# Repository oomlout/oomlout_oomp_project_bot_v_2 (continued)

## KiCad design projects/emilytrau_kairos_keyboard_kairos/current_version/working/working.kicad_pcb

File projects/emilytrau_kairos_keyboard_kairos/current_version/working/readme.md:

# kairos_keyboard
 
## summary 
* id: emilytrau_kairos_keyboard_kairos
* user: emilytrau
* name: kairos_keyboard
* board: kairos
* repo: https://github.com/emilytrau/Kairos_Keyboard
* src_file_repo_kicad_pcb: Kairos.kicad_pcb
* src_file_repo_kicad_pcb_link: https://github.com/emilytrau/Kairos_Keyboard/tree/master/Kairos.kicad_pcb

* src_file_repo_sch: Kairos.sch
* src_file_repo_sch_link: https://github.com/emilytrau/Kairos_Keyboard/tree/master/Kairos.sch
* full details link: https://github.com/oomlout/oomlout_oomp_project_bot_v_2/tree/main/projects/emilytrau_kairos_keyboard_kairos/current_version/working

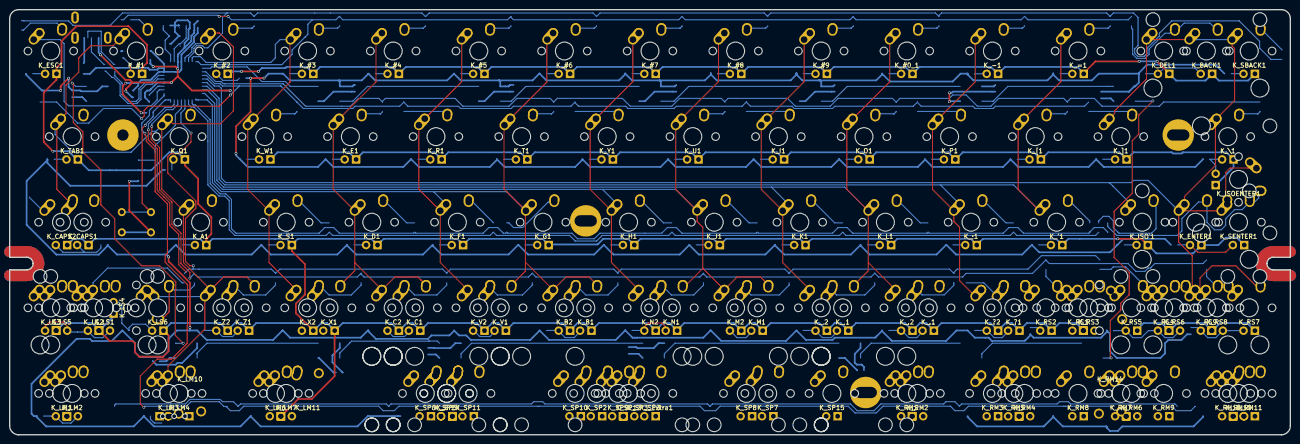
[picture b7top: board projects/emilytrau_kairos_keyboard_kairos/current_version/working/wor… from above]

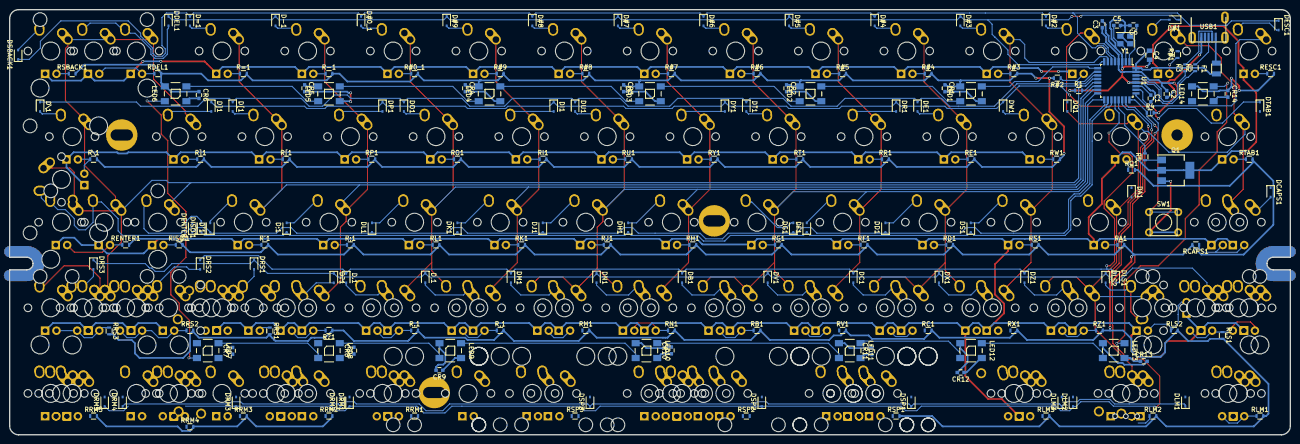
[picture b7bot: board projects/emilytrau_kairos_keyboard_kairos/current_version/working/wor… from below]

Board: 2 copper layers, 285.0 x 94.6 mm, 300 parts (183 on the bottom side), 185 nets.

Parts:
C1: 1uF; C_0603
C2, C3: 100nF; C_0603
C4: 4.7uF; C_0805
C5, C6: 22pF; C_0603
CR1, CR2, CR3, CR4, CR5, CR6, CR7, CR8, CR9, CR10, CR11, CR12, CR13, CR14: 100nF; C_0603
D#0_1, D#1, D#2, D#3, D#4, D#5, D#6, D#7, D#8, D#9: 1N4148WS; D_SOD-323
D'1: 1N4148WS; D_SOD-323
D,1: 1N4148WS; D_SOD-323
D-1: 1N4148WS; D_SOD-323
D.1: 1N4148WS; D_SOD-323
D;1: 1N4148WS; D_SOD-323
D=1: 1N4148WS; D_SOD-323
D?1: 1N4148WS; D_SOD-323
DA1: 1N4148WS; D_SOD-323
DB1: 1N4148WS; D_SOD-323
DC1: 1N4148WS; D_SOD-323
DCAPS1: 1N4148WS; D_SOD-323
DD1: 1N4148WS; D_SOD-323
DDEL1: 1N4148WS; D_SOD-323
DE1: 1N4148WS; D_SOD-323
DENTER1: 1N4148WS; D_SOD-323
DESC1: 1N4148WS; D_SOD-323
DF1: 1N4148WS; D_SOD-323
DG1: 1N4148WS; D_SOD-323
DH1: 1N4148WS; D_SOD-323
DI1: 1N4148WS; D_SOD-323
DISO`1: 1N4148WS; D_SOD-323
DJ1: 1N4148WS; D_SOD-323
DK1: 1N4148WS; D_SOD-323
DL1: 1N4148WS; D_SOD-323
DLM1, DLM2, DLM3: 1N4148WS; D_SOD-323
DLS1, DLS2: 1N4148WS; D_SOD-323
DM1: 1N4148WS; D_SOD-323
DN1: 1N4148WS; D_SOD-323
DO1: 1N4148WS; D_SOD-323
DP1: 1N4148WS; D_SOD-323
DQ1: 1N4148WS; D_SOD-323
DR1: 1N4148WS; D_SOD-323
DRM1, DRM2, DRM3, DRM4, DRM5: 1N4148WS; D_SOD-323
DRS1, DRS2, DRS3: 1N4148WS; D_SOD-323
DS1: 1N4148WS; D_SOD-323
DSBACK1: 1N4148WS; D_SOD-323
DSP1, DSP2, DSP3: 1N4148WS; D_SOD-323
DT1: 1N4148WS; D_SOD-323
DTAB1: 1N4148WS; D_SOD-323
DU1: 1N4148WS; D_SOD-323
DV1: 1N4148WS; D_SOD-323
DW1: 1N4148WS; D_SOD-323
DX1: 1N4148WS; D_SOD-323
DY1: 1N4148WS; D_SOD-323
DZ1: 1N4148WS; D_SOD-323
D[1: 1N4148WS; D_SOD-323
D\1: 1N4148WS; D_SOD-323
D]1: 1N4148WS; D_SOD-323
F1: Polyfuse; Fuse_SMD1206_Reflow
K_#0_1, K_#1, K_#2, K_#3, K_#4, K_#5, K_#6, K_#7, K_#8, K_#9: MX-1U
K_'1: MX-1U
K_,1: MX-1U-FLIPPED; MX-1U
K_,2: MX-1U
K_-1: MX-1U
K_.1: MX-1U-FLIPPED; MX-1U
K_.2: MX-1U
K_;1: MX-1U
K_=1: MX-1U
K_?1: MX-1U-FLIPPED; MX-1U
K_?2: MX-1U
K_A1: MX-1U
K_B1: MX-1U-FLIPPED; MX-1U
K_B2: MX-1U
K_BACK1: MX-2U
K_C1: MX-1U-FLIPPED; MX-1U
K_C2: MX-1U
K_CAPS1: MX-1.75U
K_CAPS2: MX-1.25U
K_D1: MX-1U
K_DEL1: MX-1U
K_E1: MX-1U
K_ENTER1: MX-2.25U
K_ESC1: MX-1U
K_F1: MX-1U
K_G1: MX-1U
K_H1: MX-1U
K_I1: MX-1U
K_ISOENTER1: MX-ISO-FLIPPED; MX-ISO-Combined
K_ISO`1: MX-1U
K_J1: MX-1U
K_K1: MX-1U
K_L1: MX-1U
K_LM1, K_LM6: MX-1.25U
K_LM2, K_LM7: MX-1.5U; MX-1.5U-FLIPPED
K_LM3: MX-1.25U; MX-1.25U-FLIPPED
K_LM4: MX-1U
K_LM10: MX-1.25U; ALPS-1.25U
K_LM11: MX-1.5U-FLIPPED; ALPS-1.5U
K_LS1: MX-2.25U-FLIPPED
K_LS2: MX-2U-FLIPPED; MX-2U
K_LS3, K_LS4, K_LS6: MX-1U
K_LS5: MX-1.25U; MX-1.25U-FLIPPED
K_M1: MX-1U-FLIPPED; MX-1U
K_M2: MX-1U
K_N1: MX-1U-FLIPPED; MX-1U
K_N2: MX-1U
K_O1: MX-1U
K_P1: MX-1U
K_Q1: MX-1U
K_R1: MX-1U
K_RM1, K_RM7, K_RM11: MX-1U
K_RM2, K_RM4, K_RM6, K_RM10: MX-1.25U; MX-1.25U-FLIPPED
K_RM3, K_RM8, K_RM9: MX-1U-FLIPPED; MX-1U
K_RM5, K_RM12: MX-1.5U
K_RM14: MX-1.25U; ALPS-1.25U
K_RS1, K_RS4, K_RS7: MX-1U-FLIPPED; MX-1U
K_RS2, K_RS5: MX-1.75U
K_RS3: MX-1.25U-FLIPPED
K_RS6: MX-2.75U-FLIPPED
K_RS8: MX-1.75U; MX-1.75U-FLIPPED
K_RS9: MX-2U
K_RS10: KEYSW; MX_100
K_S1: MX-1U
K_SBACK1: MX-1U
K_SENTER1: MX-1.25U; MX-1U
K_SP2: MX-6.25U; MX-6.25U-ReversedStabilizers
K_SP3: MX-7U; MX-7U-ReversedStabilizers
K_SP3_Extra1: MX-6U; MX-6U-7UOverlay
K_SP5: MX-2.75U; MX-2.75U-ReversedStabilizer
K_SP6: MX-2.25U-FLIPPED; MX-2.25U-ReversedStabilizer
K_SP7, K_SP14: MX-2.25U; MX-2.25U-ReversedStabilizer
K_SP8, K_SP11, K_SP15: MX-2.75U-FLIPPED; MX-2.75U-ReversedStabilizer
K_SP9, K_SP10: MX-1.25U-FLIPPED; MX-1.25U
K_SP13: MX-2U-FLIPPED; MX-2U-ReversedStabilizers-FLIPPED
K_T1: MX-1U
K_TAB1: MX-1.5U
K_U1: MX-1U
K_V1: MX-1U-FLIPPED; MX-1U
K_V2: MX-1U
K_W1: MX-1U
K_X1: MX-1U-FLIPPED; MX-1U
K_X2: MX-1U
K_Y1: MX-1U
K_Z1: MX-1U-FLIPPED; MX-1U
K_Z2: MX-1U
K_[1: MX-1U
K_\1: MX-1.5U
K_]1: MX-1U
LED1, LED2, LED3, LED4, LED5, LED6, LED7, LED8, LED9, LED10, LED11, LED12, LED13, LED14: WS2812B
Q1: NSS40301MZ4T1G; SOT-223-3Lead_TabPin2
R1, R4: 10k; R_0603
R2, R3: 22; R_0603
R5: 1.5k; R_0603
R#0_1, R#1, R#2, R#3, R#4, R#5, R#6, R#7, R#8, R#9: 2.2k; R_0603
R'1: 2.2k; R_0603
R,1: 2.2k; R_0603
R-1: 2.2k; R_0603
R.1: 2.2k; R_0603
R;1: 2.2k; R_0603
R=1: 2.2k; R_0603
R?1: 2.2k; R_0603
RA1: 2.2k; R_0603
RB1: 2.2k; R_0603
RC1: 2.2k; R_0603
RCAPS1: 2.2k; R_0603
RD1: 2.2k; R_0603
RDEL1: 2.2k; R_0603
RE1: 2.2k; R_0603
RENTER1: 2.2k; R_0603
RESC1: 2.2k; R_0603
RF1: 2.2k; R_0603
RG1: 2.2k; R_0603
RH1: 2.2k; R_0603
RI1: 2.2k; R_0603
RISO`1: 2.2k; R_0603
RJ1: 2.2k; R_0603
RK1: 2.2k; R_0603
RL1: 2.2k; R_0603
RLM1, RLM2, RLM3: 2.2k; R_0603
RLS1, RLS2: 2.2k; R_0603
RM1: 2.2k; R_0603
RN1: 2.2k; R_0603
RO1: 2.2k; R_0603
RP1: 2.2k; R_0603
RQ1: 2.2k; R_0603
RR1: 2.2k; R_0603
RRM1, RRM2, RRM3, RRM4, RRM5: 2.2k; R_0603
RRS1, RRS2, RRS3: 2.2k; R_0603
RS1: 2.2k; R_0603
RSBACK1: 2.2k; R_0603
RSP1, RSP2, RSP3: 2.2k; R_0603
RT1: 2.2k; R_0603
RTAB1: 2.2k; R_0603
RU1: 2.2k; R_0603
RV1: 2.2k; R_0603
RW1: 2.2k; R_0603
RX1: 2.2k; R_0603
RY1: 2.2k; R_0603
RZ1: 2.2k; R_0603
R[1: 2.2k; R_0603
R\1: 2.2k; R_0603
R]1: 2.2k; R_0603
SW1: SW_RST1; PushButton_6x6mm_TH
U1: ATMEGA32U2-AU; TQFP-32_7x7mm_Pitch0.8mm
USB1: Molex-0548190589
Y1: Crystal_GND24; Crystal_SMD_3225-4pin_3.2x2.5mm

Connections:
+5V: C2.1, C3.1, C4.1, CR1.1, CR2.1, CR3.1, CR4.1, CR5.1, CR6.1, CR7.1, CR8.1, CR9.1, CR10.1, CR11.1, CR12.1, CR13.1, CR14.1, F1.1, LED1.1, LED2.1, LED3.1, LED4.1, LED5.1, LED6.1, LED7.1, LED8.1, LED9.1, LED10.1, LED11.1, LED12.1, LED13.1, LED14.1, R4.2, R#0_1.2, R#1.2, R#2.2, R#3.2, R#4.2, R#5.2, R#6.2, R#7.2, R#8.2, R#9.2, R'1.2, R,1.2, R-1.2, R.1.2, R;1.2, R=1.2, R?1.1, RA1.2, RB1.2, RC1.2, RCAPS1.2, RD1.2, RDEL1.2, RE1.2, RENTER1.2, RESC1.2, RF1.2, RG1.2, RH1.2, RI1.2, RISO`1.2, RJ1.2, RK1.2, RL1.2, RLM1.2, RLM2.2, RLM3.2, RLS1.2, RLS2.2, RM1.2, RN1.2, RO1.2, RP1.2, RQ1.2, RR1.2, RRM1.2, RRM2.2, RRM3.2, RRM4.2, RRM5.2, RRS1.2, RRS2.2, RRS3.2, RS1.2, RSBACK1.2, RSP1.2, RSP2.2, RSP3.2, RT1.2, RTAB1.2, RU1.2, RV1.2, RW1.2, RX1.2, RY1.2, RZ1.2, R[1.2, R\1.2, R]1.2, U1.4, U1.31, U1.32
COL0: K_ESC1.1, K_LM1.1, K_LM2.1, K_LS1.2, K_LS2.2, K_LS3.1, K_LS5.1, U1.26
COL1: K_#1.1, K_#2.1, K_A1.1, K_CAPS1.1, K_CAPS2.2, K_LM3.1, K_LM4.1, K_LM6.1, K_LM7.1, K_LM10.1, K_LM11.2, K_LS4.1, K_LS6.1, K_Q1.1, K_TAB1.1, K_Z1.2, K_Z2.1, U1.5
COL2: K_#3.1, K_#4.1, K_C1.2, K_C2.1, K_D1.1, K_E1.1, K_S1.1, K_W1.1, K_X1.2, K_X2.1, U1.7
COL3: K_#5.1, K_#6.1, K_B1.2, K_B2.1, K_F1.1, K_G1.1, K_R1.1, K_SP2.1, K_SP3.1, K_SP5.1, K_SP6.2, K_SP9.2, K_SP10.2, K_SP11.2, K_SP13.2, K_SP14.1, K_T1.1, K_V1.2, K_V2.1, U1.17
COL4: K_#7.1, K_#8.1, K_H1.1, K_J1.1, K_M1.2, K_M2.1, K_N1.2, K_N2.1, K_SP7.1, K_SP8.2, K_SP15.2, K_U1.1, K_Y1.1, U1.16
COL5: K_#0_1.1, K_#9.1, K_,1.2, K_,2.1, K_.1.2, K_.2.1, K_I1.1, K_K1.1, K_L1.1, K_O1.1, K_RM1.1, K_RM2.1, U1.15
COL6: K_'1.1, K_-1.1, K_;1.1, K_=1.1, K_?1.2, K_?2.1, K_P1.1, K_RM3.2, K_RM4.1, K_RM5.1, K_RM8.2, K_RS1.2, K_RS2.1, K_RS3.2, K_[1.1, U1.14
COL7: K_BACK1.1, K_DEL1.1, K_ENTER1.1, K_ISOENTER1.2, K_ISO`1.1, K_RM6.1, K_RM7.1, K_RM9.2, K_RM10.1, K_RM11.1, K_RM12.1, K_RM14.1, K_RS4.2, K_RS5.1, K_RS6.2, K_RS7.2, K_RS8.1, K_RS9.1, K_RS10.2, K_SBACK1.1, K_SENTER1.1, K_\1.1, K_]1.1, U1.12
DM: R3.2, USB1.4
DP: R2.2, USB1.3
GND: C1.2, C2.2, C3.2, C4.2, C5.2, C6.2, CR1.2, CR2.2, CR3.2, CR4.2, CR5.2, CR6.2, CR7.2, CR8.2, CR9.2, CR10.2, CR11.2, CR12.2, CR13.2, CR14.2, LED1.3, LED2.3, LED3.3, LED4.3, LED5.3, LED6.3, LED7.3, LED8.3, LED9.3, LED10.3, LED11.3, LED12.3, LED13.3, LED14.3, Q1.3, R1.1, SW1.1, U1.3, U1.28, USB1.1, Y1.2, Y1.4
LEDGND: K_#0_1.4, K_#1.4, K_#2.4, K_#3.4, K_#4.4, K_#5.4, K_#6.4, K_#7.4, K_#8.4, K_#9.4, K_'1.4, K_,1.4, K_,2.4, K_-1.4, K_.1.4, K_.2.4, K_;1.4, K_=1.4, K_?1.4, K_?2.4, K_A1.4, K_B1.4, K_B2.4, K_BACK1.4, K_C1.4, K_C2.4, K_CAPS1.4, K_CAPS2.4, K_D1.4, K_DEL1.4, K_E1.4, K_ENTER1.4, K_ESC1.4, K_F1.4, K_G1.4, K_H1.4, K_I1.4, K_ISOENTER1.4, K_ISO`1.4, K_J1.4, K_K1.4, K_L1.4, K_LM1.4, K_LM2.4, K_LM3.4, K_LM6.4, K_LM7.4, K_LS1.4, K_LS2.4, K_LS3.4, K_LS4.4, K_LS5.4, K_LS6.4, K_M1.4, K_M2.4, K_N1.4, K_N2.4, K_O1.4, K_P1.4, K_Q1.4, K_R1.4, K_RM1.4, K_RM2.4, K_RM3.4, K_RM4.4, K_RM5.4, K_RM6.4, K_RM7.4, K_RM8.4, K_RM9.4, K_RM10.4, K_RM11.4, K_RM12.4, K_RS1.4, K_RS2.4, K_RS3.4, K_RS4.4, K_RS5.4, K_RS6.4, K_RS7.4, K_RS8.4, K_RS9.4, K_S1.4, K_SBACK1.4, K_SENTER1.4, K_SP2.4, K_SP3.4, K_SP5.4, K_SP6.4, K_SP7.4, K_SP8.4, K_SP9.4, K_SP10.4, K_SP11.4, K_SP13.4, K_SP14.4, K_SP15.4, K_T1.4, K_TAB1.4, K_U1.4, K_V1.4, K_V2.4, K_W1.4, K_X1.4, K_X2.4, K_Y1.4, K_Z1.4, K_Z2.4, K_[1.4, K_\1.4, K_]1.4, Q1.2
unnamed: C1.1, U1.27
unnamed: C5.1, U1.2, Y1.3
unnamed: C6.1, U1.1, Y1.1
unnamed: D#0_1.2, K_#0_1.2
unnamed: D#1.2, K_#1.2
unnamed: D#2.2, K_#2.2
unnamed: D#3.2, K_#3.2
unnamed: D#4.2, K_#4.2
unnamed: D#5.2, K_#5.2
unnamed: D#6.2, K_#6.2
unnamed: D#7.2, K_#7.2
unnamed: D#8.2, K_#8.2
unnamed: D#9.2, K_#9.2
unnamed: D'1.2, K_'1.2
unnamed: D,1.2, K_,1.1, K_,2.2
unnamed: D-1.2, K_-1.2
unnamed: D.1.2, K_.1.1, K_.2.2
unnamed: D;1.2, K_;1.2
unnamed: D=1.2, K_=1.2
unnamed: D?1.2, K_?1.1, K_?2.2
unnamed: DA1.2, K_A1.2
unnamed: DB1.2, K_B1.1, K_B2.2
unnamed: DC1.2, K_C1.1, K_C2.2
unnamed: DCAPS1.2, K_CAPS1.2, K_CAPS2.1
unnamed: DD1.2, K_D1.2
unnamed: DDEL1.2, K_BACK1.2, K_DEL1.2
unnamed: DE1.2, K_E1.2
unnamed: DENTER1.2, K_ENTER1.2, K_ISOENTER1.1, K_SENTER1.2
unnamed: DESC1.2, K_ESC1.2
unnamed: DF1.2, K_F1.2
unnamed: DG1.2, K_G1.2
unnamed: DH1.2, K_H1.2
unnamed: DI1.2, K_I1.2
unnamed: DISO`1.2, K_ISO`1.2
unnamed: DJ1.2, K_J1.2
unnamed: DK1.2, K_K1.2
unnamed: DL1.2, K_L1.2
unnamed: DLM1.2, K_LM1.2, K_LM2.2
unnamed: DLM2.2, K_LM3.2, K_LM4.2, K_LM10.2
unnamed: DLM3.2, K_LM6.2, K_LM7.2, K_LM11.1
unnamed: DLS1.2, K_LS1.1, K_LS2.1, K_LS3.2, K_LS5.2
unnamed: DLS2.2, K_LS4.2, K_LS6.2
unnamed: DM1.2, K_M1.1, K_M2.2
unnamed: DN1.2, K_N1.1, K_N2.2
unnamed: DO1.2, K_O1.2
unnamed: DP1.2, K_P1.2
unnamed: DQ1.2, K_Q1.2
unnamed: DR1.2, K_R1.2
unnamed: DRM1.2, K_RM1.2, K_RM2.2
unnamed: DRM2.2, K_RM3.1, K_RM4.2, K_RM5.2
unnamed: DRM3.2, K_RM8.1
unnamed: DRM4.2, K_RM6.2, K_RM7.2, K_RM9.1, K_RM14.2
unnamed: DRM5.2, K_RM10.2, K_RM11.2, K_RM12.2
unnamed: DRS1.2, K_RS1.1, K_RS2.2, K_RS3.1
unnamed: DRS2.2, K_RS4.1, K_RS5.2, K_RS6.1, K_RS10.1
unnamed: DRS3.2, K_RS7.1, K_RS8.2, K_RS9.2
unnamed: DS1.2, K_S1.2
unnamed: DSBACK1.2, K_SBACK1.2
unnamed: DSP1.2, K_SP5.2, K_SP6.1, K_SP11.1, K_SP14.2
unnamed: DSP2.2, K_SP2.2, K_SP3.2, K_SP9.1, K_SP10.1, K_SP13.1
unnamed: DSP3.2, K_SP7.2, K_SP8.1, K_SP15.1
unnamed: DT1.2, K_T1.2
unnamed: DTAB1.2, K_TAB1.2
unnamed: DU1.2, K_U1.2
unnamed: DV1.2, K_V1.1, K_V2.2
unnamed: DW1.2, K_W1.2
unnamed: DX1.2, K_X1.1, K_X2.2
unnamed: DY1.2, K_Y1.2
unnamed: DZ1.2, K_Z1.1, K_Z2.2
unnamed: D[1.2, K_[1.2
unnamed: D\1.2, K_\1.2
unnamed: D]1.2, K_]1.2
unnamed: K_#0_1.3, R#0_1.1
unnamed: K_#1.3, R#1.1
unnamed: K_#2.3, R#2.1
unnamed: K_#3.3, R#3.1
unnamed: K_#4.3, R#4.1
unnamed: K_#5.3, R#5.1
unnamed: K_#6.3, R#6.1
unnamed: K_#7.3, R#7.1
unnamed: K_#8.3, R#8.1
unnamed: K_#9.3, R#9.1
unnamed: K_'1.3, R'1.1
unnamed: K_,1.3, K_,2.3, R,1.1
unnamed: K_-1.3, R-1.1
unnamed: K_.1.3, K_.2.3, R.1.1
unnamed: K_;1.3, R;1.1
unnamed: K_=1.3, R=1.1
unnamed: K_?1.3, K_?2.3, R?1.2
unnamed: K_A1.3, RA1.1
unnamed: K_B1.3, K_B2.3, RB1.1
unnamed: K_BACK1.3, K_DEL1.3, RDEL1.1
unnamed: K_C1.3, K_C2.3, RC1.1
unnamed: K_CAPS1.3, K_CAPS2.3, RCAPS1.1
unnamed: K_D1.3, RD1.1
unnamed: K_E1.3, RE1.1
unnamed: K_ENTER1.3, K_SENTER1.3, RENTER1.1
unnamed: K_ESC1.3, RESC1.1
unnamed: K_F1.3, RF1.1
unnamed: K_G1.3, RG1.1
unnamed: K_H1.3, RH1.1
unnamed: K_I1.3, RI1.1
unnamed: K_ISOENTER1.3, K_\1.3, R\1.1
unnamed: K_ISO`1.3, RISO`1.1
unnamed: K_J1.3, RJ1.1
unnamed: K_K1.3, RK1.1
unnamed: K_L1.3, RL1.1
unnamed: K_LM1.3, K_LM2.3, RLM1.1
unnamed: K_LM3.3, K_LM4.3, RLM2.1
unnamed: K_LM6.3, K_LM7.3, RLM3.1
unnamed: K_LS1.3, K_LS2.3, K_LS3.3, K_LS5.3, RLS1.1
unnamed: K_LS4.3, K_LS6.3, RLS2.1
unnamed: K_M1.3, K_M2.3, RM1.1
unnamed: K_N1.3, K_N2.3, RN1.1
unnamed: K_O1.3, RO1.1
unnamed: K_P1.3, RP1.1
unnamed: K_Q1.3, RQ1.1
unnamed: K_R1.3, RR1.1
unnamed: K_RM1.3, K_RM2.3, RRM1.1
unnamed: K_RM3.3, K_RM4.3, K_RM5.3, RRM2.1
unnamed: K_RM8.3, RRM3.1
unnamed: K_RM10.3, K_RM11.3, K_RM12.3, RRM5.1
unnamed: K_RM6.3, K_RM7.3, K_RM9.3, RRM4.1
unnamed: K_RS1.3, K_RS2.3, K_RS3.3, RRS1.1
unnamed: K_RS4.3, K_RS5.3, K_RS6.3, RRS2.1
unnamed: K_RS7.3, K_RS8.3, K_RS9.3, RRS3.1
unnamed: K_S1.3, RS1.1
unnamed: K_SBACK1.3, RSBACK1.1
unnamed: K_SP2.3, K_SP3.3, K_SP9.3, K_SP10.3, K_SP13.3, RSP2.1
unnamed: K_SP5.3, K_SP6.3, K_SP11.3, K_SP14.3, RSP1.1
unnamed: K_SP7.3, K_SP8.3, K_SP15.3, RSP3.1
unnamed: K_T1.3, RT1.1
unnamed: K_TAB1.3, RTAB1.1
unnamed: K_U1.3, RU1.1
unnamed: K_V1.3, K_V2.3, RV1.1
unnamed: K_W1.3, RW1.1
unnamed: K_X1.3, K_X2.3, RX1.1
unnamed: K_Y1.3, RY1.1
unnamed: K_Z1.3, K_Z2.3, RZ1.1
unnamed: K_[1.3, R[1.1
unnamed: K_]1.3, R]1.1
unnamed: LED1.2, LED2.4
unnamed: LED2.2, LED3.4
unnamed: LED3.2, LED4.4
unnamed: LED4.2, LED5.4
unnamed: LED5.2, LED6.4
unnamed: LED6.2, LED7.4
unnamed: LED7.2, LED8.4
unnamed: LED8.2, LED9.4
unnamed: LED10.2, LED11.4
unnamed: LED9.2, LED10.4
unnamed: LED11.2, LED12.4
unnamed: LED12.2, LED13.4
unnamed: LED13.2, LED14.4
unnamed: Q1.1, R5.1
unnamed: R1.2, U1.13
unnamed: R2.1, U1.29
unnamed: R3.1, U1.30
unnamed: R4.1, SW1.2, U1.24
unnamed: R5.2, U1.21
RGBLED: LED1.4, U1.9
ROW0: D#0_1.1, D#2.1, D#4.1, D#6.1, D#8.1, D=1.1, DESC1.1, DSBACK1.1, U1.6
ROW1: D#1.1, D#3.1, D#5.1, D#7.1, D#9.1, D-1.1, DDEL1.1, U1.8
ROW2: DE1.1, DO1.1, DQ1.1, DT1.1, DU1.1, D[1.1, D\1.1, U1.10
ROW3: DI1.1, DP1.1, DR1.1, DTAB1.1, DW1.1, DY1.1, D]1.1, U1.11
ROW4: D'1.1, DA1.1, DD1.1, DENTER1.1, DG1.1, DJ1.1, DL1.1, U1.18
ROW5: D;1.1, DCAPS1.1, DF1.1, DH1.1, DISO`1.1, DK1.1, DS1.1, U1.19
ROW6: D.1.1, DB1.1, DC1.1, DLS1.1, DM1.1, DRS2.1, DZ1.1, U1.20
ROW7: D,1.1, D?1.1, DLS2.1, DN1.1, DRS1.1, DRS3.1, DV1.1, DX1.1, U1.22
ROW8: DLM1.1, DLM3.1, DRM2.1, DRM4.1, DSP1.1, DSP3.1, U1.23
ROW9: DLM2.1, DRM1.1, DRM3.1, DRM5.1, DSP2.1, U1.25
VCC: F1.2, USB1.5
